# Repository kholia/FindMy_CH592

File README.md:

# CH592 Find My tracker firmware

This firmware supports Apple Find My, Google's Find My Device / Find Hub
Network, or both networks from one CH592 binary. Dual mode alternates complete
Apple and Google advertisements every 30 seconds because each frame consumes
nearly all of the 31-byte legacy BLE advertising payload.

### Usage

Get https://github.com/WeActStudio/WeActStudio.WCH-BLE-Core 'CH592F' board(s).

Set up the repository:

```
git clone https://github.com/kholia/FindMy_CH592.git && cd FindMy_CH592

python3 -m venv venv

source venv/bin/activate

pip install -r requirements.txt
```

Generate one or more key(s):
   
```
./generate_keys.py
```

Prepare an Apple Find My firmware:

```
./prep_fw.py --keyfile first.keys second.keys third.keys --adv-interval=2 --firmware main.bin --output flashme.bin
```

For Google Find Hub, register the tracker using
`GoogleFindMyTools-main/main.py`, then copy the 40-character
`Advertisement Key` printed by that flow:

```
./prep_fw.py --google-eid 00112233445566778899aabbccddeeff00112233 \
  --adv-interval 3 --firmware main.bin --output flashme.bin
```

To advertise on both networks, pass both credential types:

```
./prep_fw.py --keyfile device.keys \
  --google-eid 00112233445566778899aabbccddeeff00112233 \
  --adv-interval 3 --firmware main.bin --output flashme.bin
```

Dual mode alternates networks every 30 seconds. Multiple Apple keys still
rotate hourly. Network switching does not change the Bluetooth address; only
an Apple key rotation changes it. Google-only mode uses the CH592 factory
address, matching the reference Google firmwares, and uses `--google-eid` only
for the FMDN service-data EID.

After provisioning, `prep_fw.py` prints the expected initial Apple address and
Google advertisement EID. Compare those values with an on-air capture to catch
an incorrect credential or accidentally flashed image immediately.

The Google support matches the experimental simple beacon in
`GoogleFindMyTools-main`: it advertises one fixed 20-byte EID and does not
implement Fast Pair or on-device EID derivation. Its current workflow requires
periodically re-announcing the advertisement key to Google, and locations are
queried through GoogleFindMyTools rather than the official app.

Flash the firmware:

```
./flash.sh
```

### Further preparation [OPTIONAL]

```
sqlite3 reports.db 'CREATE TABLE reports (id_short TEXT, timestamp INTEGER, datePublished INTEGER, payload TEXT, id TEXT, statusCode INTEGER, PRIMARY KEY(id_short,timestamp))'
```

```
docker network create mh-network

docker run -d --restart always --name anisette -p 6969:6969 --volume anisette-v3_data:/home/Alcoholic/.config/anisette-v3 --network mh-network dadoum/anisette-v3-server
```

Note: You will be asked for your Apple-ID, password and your 2FA. If you see
serving at port 6176 over HTTP you have all set up correctly. 

```
$ ./request_reports.py
pyprovision is not installed, querying http://localhost:6969 for an anisette server
200: 8 reports received.
...
```

### References

- Android app => https://github.com/parawanderer/OpenTagViewer - Use this!

  ```
  qrencode -r XYZ_devices.json -o sensitive.png

  open sensitive.png
  ```

  Scan this with the `OpenTagViewer` Android app

- https://github.com/biemster/qible

- https://github.com/dchristl/macless-haystack

- https://github.com/biemster/FindMy

- https://github.com/malmeloo/FindMy.py

- https://www.wch.cn/downloads/CH592EVT_ZIP.html

### PS

- While you can create HW tags at a (much) lower cost, this work presents a
  good balance of convenience, cost, and performance.

- Use `nRF Connect for Mobile` Android app for seeing these beacons in action.

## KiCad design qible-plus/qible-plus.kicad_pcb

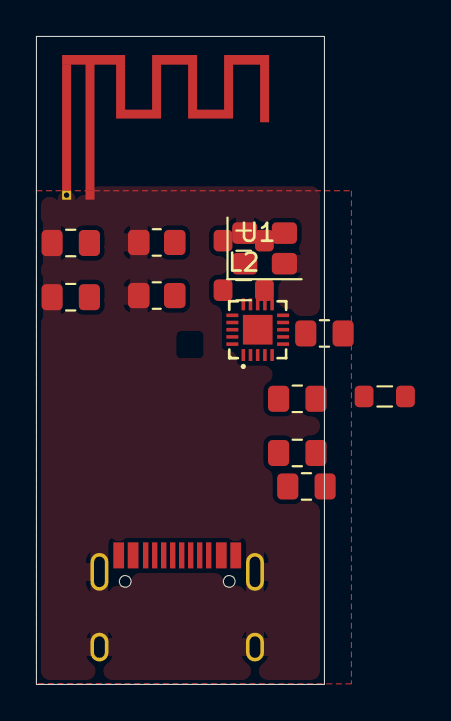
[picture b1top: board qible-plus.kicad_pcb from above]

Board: 2 copper layers, 16.0 x 36.0 mm, 16 parts (1 on the bottom side), 13 nets, no tracks yet.

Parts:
AE1: Antenna_Dipole; Blaze_2.4GHz_MIFA
C1: 0.47uF; C_0805_2012Metric_Pad1.18x1.45mm_HandSolder
C2, C5, C6: 0.1uF; C_0805_2012Metric_Pad1.18x1.45mm_HandSolder
C3: 4.7uF; C_0805_2012Metric_Pad1.18x1.45mm_HandSolder
C4: 2.2u; C_0805_2012Metric_Pad1.18x1.45mm_HandSolder
FB6: BLM21BD102SN1D; L_0805_2012Metric_Pad1.05x1.20mm_HandSolder
J1: USB; USB_C_Receptacle_HRO_TYPE-C-31-M-12-Modded
L1: 10uH; L_0805_2012Metric_Pad1.05x1.20mm_HandSolder
L2: L; L_0805_2012Metric_Pad1.05x1.20mm_HandSolder
R3, R5: 5K1; R_0805_2012Metric_Pad1.20x1.40mm_HandSolder
U1: CH591D; QFN-20_L3.0-W3.0-P0.40-BL-EP1.7
U2: MY-2032-16; BAT-SMD_MY-2032-16
X1: 32MHz; Crystal_SMD_3225-4Pin_3.2x2.5mm

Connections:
+3.3V: C2.1, C3.1, C4.1, L1.1, U1.3 (VDCID), U1.5 (VIO33/VDD33), U1.16 (VDCIA), U2.1, U2.2
GND: AE1.2, C1.2, C2.2, C3.2, C4.2, C5.1, C6.1, J1.A1 (GND), J1.A12 (GND), J1.B1 (GND), J1.B12 (GND), J1.S1 (SHIELD), R3.1, R5.1, U1.21 (GND), U2.3, X1.2, X1.4
unnamed: AE1.1, C6.2, L2.2
unnamed: FB6.1, J1.A4 (VBUS), J1.A9 (VBUS), J1.B4 (VBUS), J1.B9 (VBUS)
unnamed: J1.A5 (CC1), R5.2
unnamed: J1.B5 (CC2), R3.2
unnamed: C5.2, L2.1, U1.15 (ANT)
unnamed: C1.1, U1.14 (VINTA)
unnamed: L1.2, U1.4 (VSW)
unnamed: U1.13 (X32MI), X1.1
unnamed: U1.12 (X32MO), X1.3
UD+: J1.A6 (D+), J1.B6 (D+), U1.8 (PB11/UD+/TMR2_)
UD-: J1.A7 (D-), J1.B7 (D-), U1.9 (PB10/UD-/TMR1_)

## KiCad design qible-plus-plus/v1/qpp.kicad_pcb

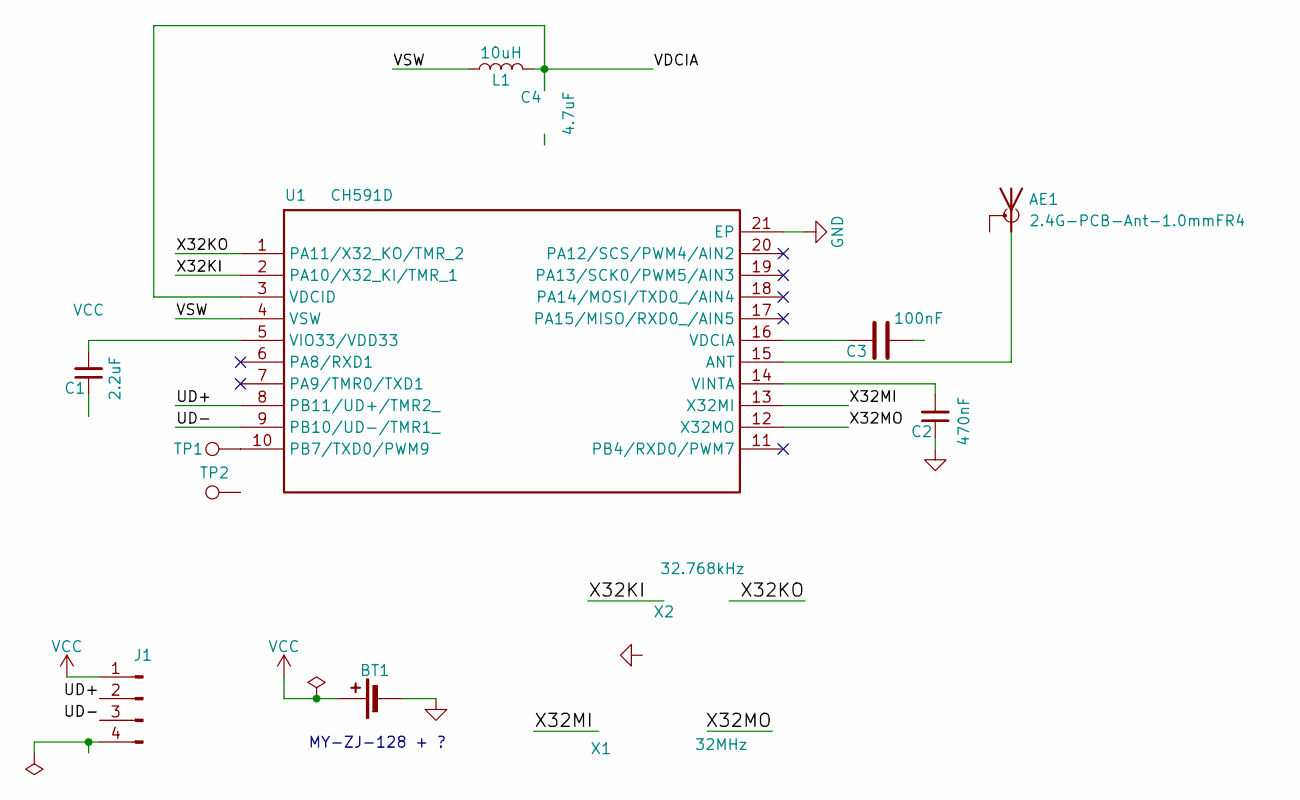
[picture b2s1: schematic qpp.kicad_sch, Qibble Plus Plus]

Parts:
AE1: 2.4G-PCB-Ant-1.0mmFR4; ant-f-2.4g-1.0mmfr4
BT1: CR2032 Holder
C1: 2.2uF; C_0805_2012Metric_Pad1.18x1.45mm_HandSolder
C2: 470nF; C_0805_2012Metric_Pad1.18x1.45mm_HandSolder
C3: 100nF; C_0805_2012Metric_Pad1.18x1.45mm_HandSolder
C4: 4.7uF; C_0805_2012Metric_Pad1.18x1.45mm_HandSolder
J1: DL-2.0
L1: 10uH; L_1008_2520Metric_Pad1.43x2.20mm_HandSolder
TP1, TP2: TestPoint; TestPoint_Pad_1.0x1.0mm
U1: CH591D; QFN-20_L3.0-W3.0-P0.40-BL-EP1.7; Manufacturer Part CH591D; LCSC Part Name CH591D
X1: 32MHz; CRYSTAL-SMD_4P-L3.2-W2.5-BL
X2: 32.768kHz; OSC-SMD_L3.2-W1.5

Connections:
/UD+: J1.2, U1.8 (PB11/UD+/TMR2_)
/UD-: J1.3, U1.9 (PB10/UD-/TMR1_)
/VDCIA: C4.1, L1.2, U1.3 (VDCID)
/VSW: L1.1, U1.4 (VSW)
/X32KI: U1.2 (PA10/X32_KI/TMR_1), X2.1
/X32KO: U1.1 (PA11/X32_KO/TMR_2), X2.2
/X32MI: U1.13 (X32MI), X1.1
/X32MO: U1.12 (X32MO), X1.3
GND: AE1.2 (GND), BT1.2 (-), C1.1, C2.1, C3.2, C4.2, J1.4, TP2.1 (1_1), U1.21 (EP), X1.2, X1.4
unnamed: AE1.1 (A), U1.15 (ANT)
unnamed: TP1.1 (1_1), U1.10 (PB7/TXD0/PWM9)
unnamed: C3.1, U1.16 (VDCIA)
unnamed: C2.2, U1.14 (VINTA)
VCC: BT1.1 (+), C1.2, J1.1, U1.5 (VIO33/VDD33)

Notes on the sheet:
MY-ZJ-128 + ?

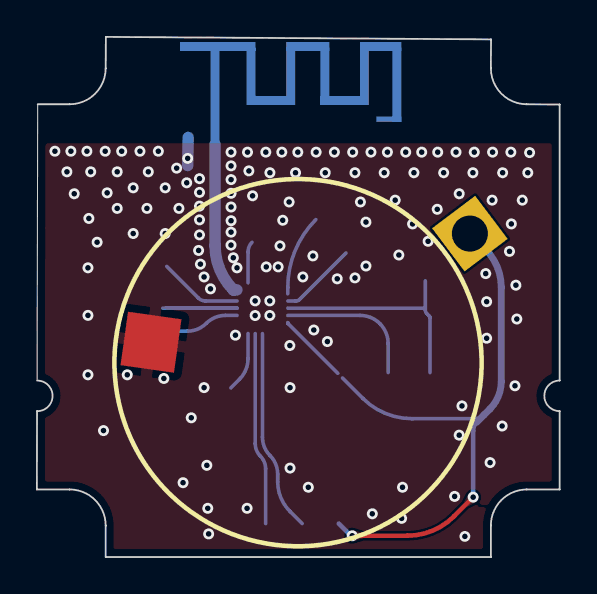
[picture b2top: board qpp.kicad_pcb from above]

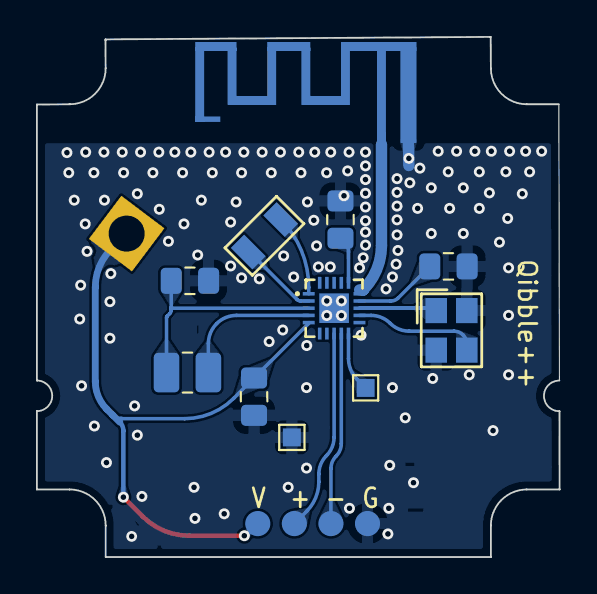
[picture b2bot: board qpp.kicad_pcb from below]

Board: 2 copper layers, 29.0 x 28.9 mm, 13 parts (12 on the bottom side), 14 nets.
